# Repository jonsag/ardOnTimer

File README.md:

# ardOnTimer
An on timer with relay, mainly for use in an UV exposure box.  

Time is set with buttons and visualized on an LCD display.  

When setting new time it's saved in eeprom and reloaded at startup.  

Timer range is from 10 seconds to 9 hours, 59 minutes and 59 seconds in 10 seconds steps.  
This can be changed in configuration file.  

Parts list
==========
1 x Arduino Uno, kjell.com art#88860  
1 x LCD display 2x16 characters, kjell.com art# 90215  
1 x Relay module KY-019, kjell.com art# 87878  
1 x Buzzer, kjell.com art# 87887  
4 x Switch, kjell.com art# 36011  
1 x 10kohm potentiometer  
4 x 10kohm resistor  
1 x 220ohm resistor  
1x 100ohm resistor  

Screens
==========
The timer has three screens.  
Second row on screens shows which buttons are active.  

Standby screen
----------
Waiting for start or set.  

 * Start/Stop/Store button to start timer and enter run screen.  
 * Set button to enter set screen.  

Run screen
----------
Shows spinning bar and time left on first row, and progressbar on the second.  

 * Start/Stop/Store button to stop timer and go back to standby screen.  

Set screen
----------
Setting timer.  

* Start/Stop/Store button to store set time.  
* Set button to exit back to standby screen. If set time was not stored, previous time will be used.  
* Up or Down button to increase/decrease time. Each press adds/subtracts 10 seconds from time. Long press adds/subtracts one minute from time. Holding down button keeps stepping minutes.

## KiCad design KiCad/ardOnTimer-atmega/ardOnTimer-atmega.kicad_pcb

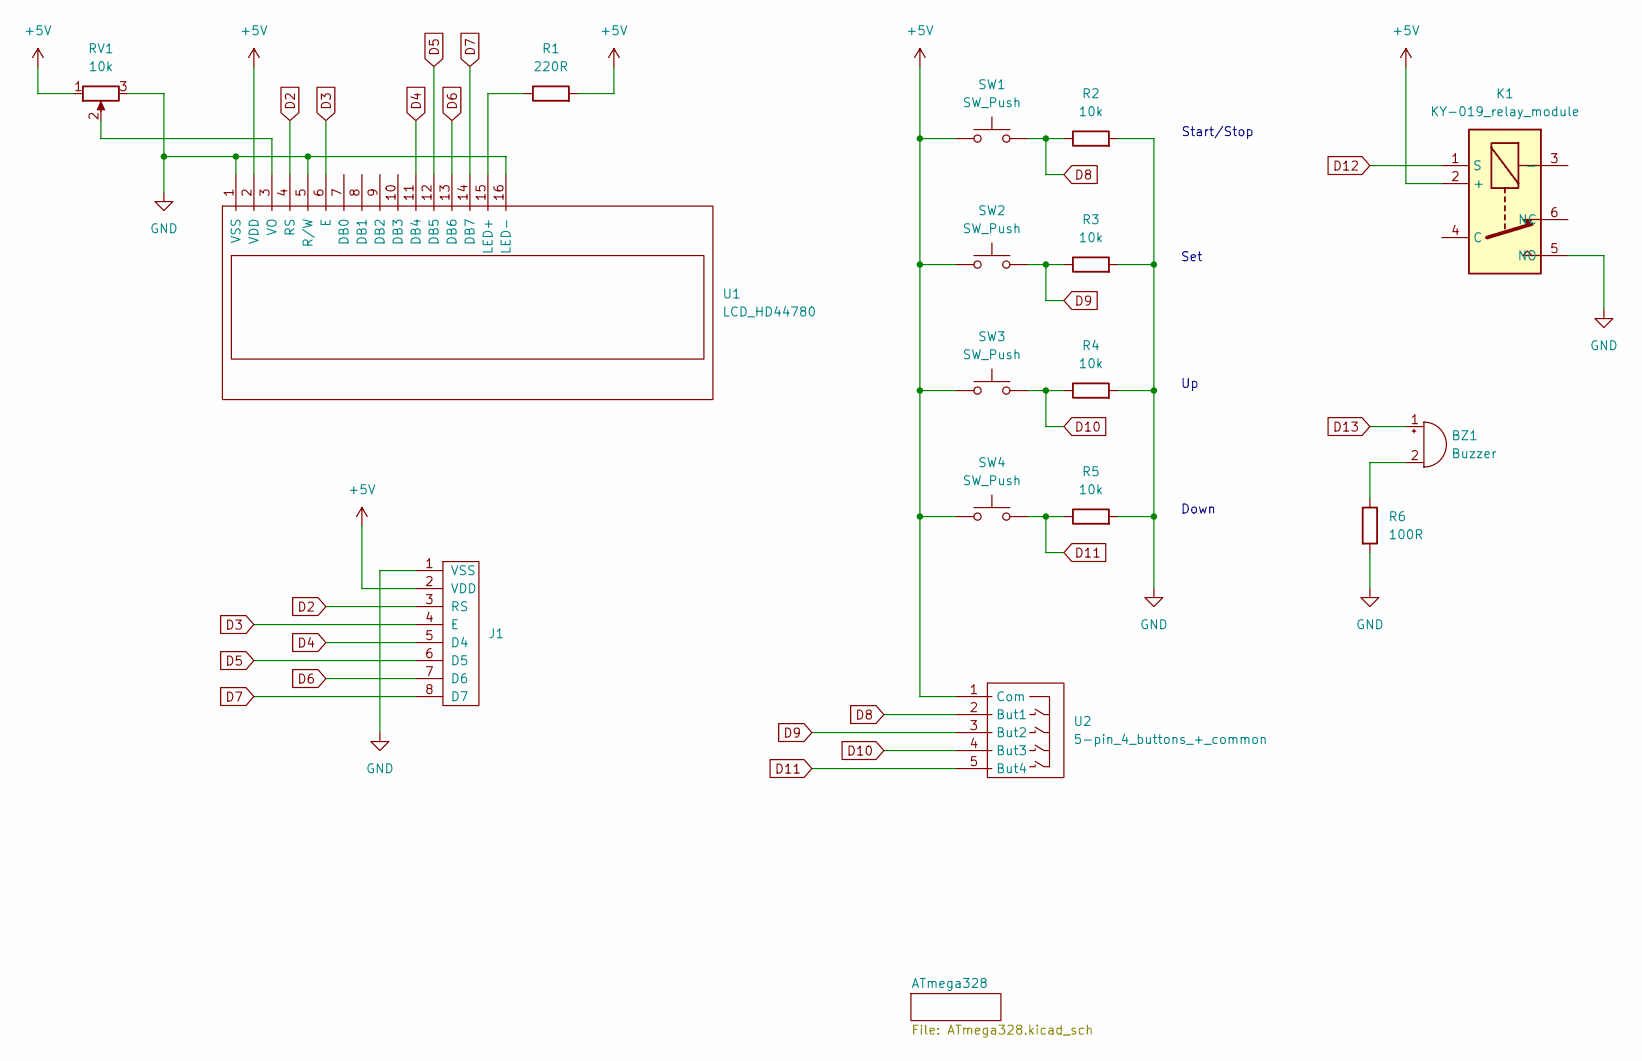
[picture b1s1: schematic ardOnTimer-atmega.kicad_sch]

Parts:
BZ1: Buzzer; Buzzer_TDK_PS1240P02BT_D12.2mm_H6.5mm_large
J1: 8-pin_header_LCD_interface; 8-pin JST LCD
K1: KY-019_relay_module; KY-019_Relay_module_w_header_large
R1: 220R; R_Axial_DIN0207_L6.3mm_D2.5mm_P10.16mm_Horizontal_larger_pa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
R2, R3, R4, R5: 10k; R_Axial_DIN0207_L6.3mm_D2.5mm_P10.16mm_Horizontal_larger_pa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
R6: 100R; R_Axial_DIN0207_L6.3mm_D2.5mm_P10.16mm_Horizontal_larger_pa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
RV1: 10k; Potentiometer_Bourns_3339P_Vertical_large
SW1, SW2, SW3, SW4: SW_Push; SW_PUSH_6mm_large
U1: LCD_HD44780; LCD_HD44780_16x2_w_headers_large
U2: 5-pin_4_buttons_+_common; 5-pin JST 4 buttons + common

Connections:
+5V: J1.2 (VDD), K1.2 (+), R1.2, RV1.1, SW1.1, SW2.1, SW3.1, SW4.1, U1.2 (VDD), U2.1 (Com); also elsewhere on the board
D2: J1.3 (RS), U1.4 (RS); also elsewhere on the board
D3: J1.4 (E), U1.6 (E); also elsewhere on the board
D4: J1.5 (D4), U1.11 (DB4); also elsewhere on the board
D5: J1.6 (D5), U1.12 (DB5); also elsewhere on the board
D6: J1.7 (D6), U1.13 (DB6); also elsewhere on the board
D7: J1.8 (D7), U1.14 (DB7); also elsewhere on the board
D8: R2.1, SW1.2, U2.2 (But1); also elsewhere on the board
D9: R3.1, SW2.2, U2.3 (But2); also elsewhere on the board
D10: R4.1, SW3.2, U2.4 (But3); also elsewhere on the board
D11: R5.1, SW4.2, U2.5 (But4); also elsewhere on the board
D12: K1.1 (S); also elsewhere on the board
D13: BZ1.1 (-); also elsewhere on the board
GND: J1.1 (VSS), K1.5 (NO), R2.2, R3.2, R4.2, R5.2, R6.2, RV1.3, U1.1 (VSS), U1.5 (R/W), U1.16 (LED-); also elsewhere on the board
unnamed: BZ1.2 (+), R6.1
unnamed: R1.1, U1.15 (LED+)
unnamed: RV1.2, U1.3 (VO)

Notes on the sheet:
Start/Stop
Down
Set

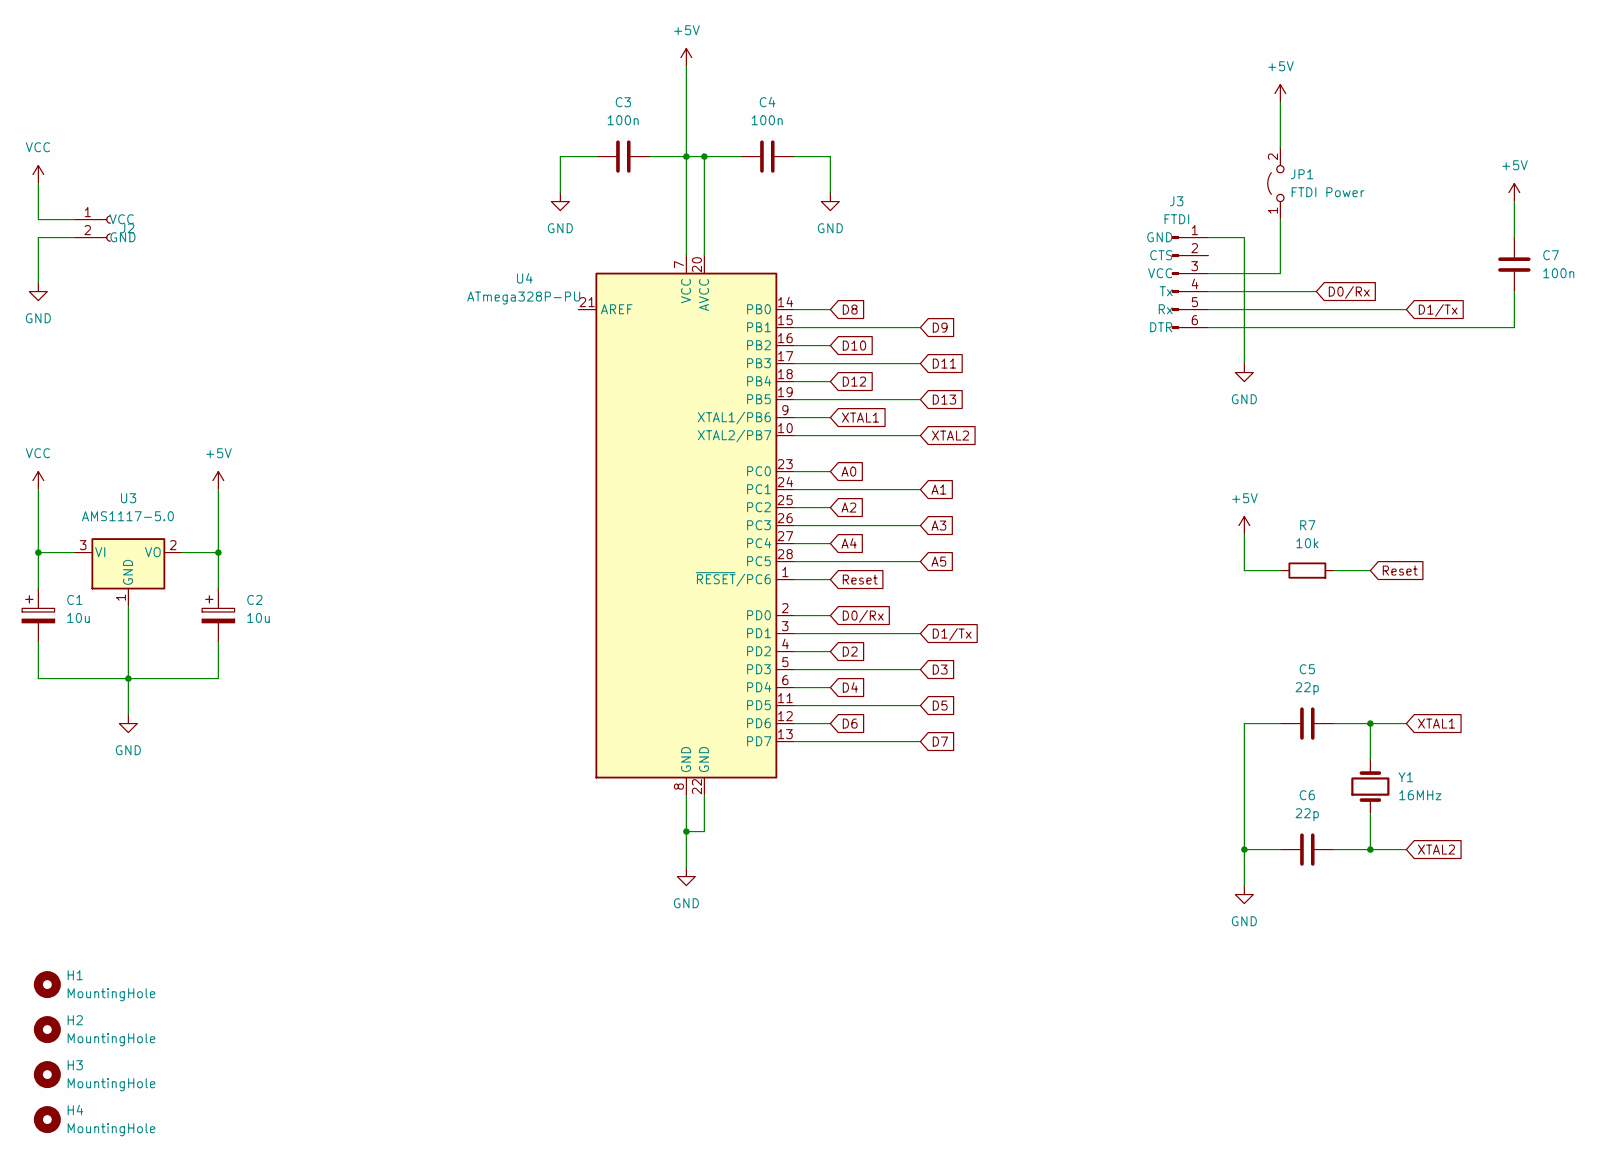
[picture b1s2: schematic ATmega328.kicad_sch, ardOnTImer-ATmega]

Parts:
C1, C2: 10u; CP_Radial_D5.0mm_P2.00mm_larger
C3, C4, C7: 100n; C_Disc_D4.3mm_W1.9mm_P5.00mm_large
C5, C6: 22p; C_Disc_D3.0mm_W1.6mm_P2.50mm_larg
H1, H2, H3, H4: MountingHole; MountingHole_3.2mm_M3
J2: Power in; BarrelJack_Horizontal
J3: FTDI; 6-pin FTDI Programmer PinSocket large
JP1: FTDI Power; Jumper_1x02_P2.54mm_large
R7: 10k; R_Axial_DIN0207_L6.3mm_D2.5mm_P10.16mm_Horizontal_larger_pa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
U3: AMS1117-5.0; SOT-223-3_TabPin2
U4: ATmega328P-PU; DIP-28_W7.62mm_LongPads w socket
Y1: 16MHz; Crystal_HC49-4H_Vertical_large

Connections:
+5V: C2.1, C3.1, C4.2, C7.2, JP1.2 (B), R7.1, U3.2 (VO), U4.7 (VCC), U4.20 (AVCC); also elsewhere on the board
A0: U4.23 (PC0)
A1: U4.24 (PC1)
A2: U4.25 (PC2)
A3: U4.26 (PC3)
A4: U4.27 (PC4)
A5: U4.28 (PC5)
D0/Rx: J3.4 (Tx), U4.2 (PD0)
D1/Tx: J3.5 (Rx), U4.3 (PD1)
D2: U4.4 (PD2); also elsewhere on the board
D3: U4.5 (PD3); also elsewhere on the board
D4: U4.6 (PD4); also elsewhere on the board
D5: U4.11 (PD5); also elsewhere on the board
D6: U4.12 (PD6); also elsewhere on the board
D7: U4.13 (PD7); also elsewhere on the board
D8: U4.14 (PB0); also elsewhere on the board
D9: U4.15 (PB1); also elsewhere on the board
D10: U4.16 (PB2); also elsewhere on the board
D11: U4.17 (PB3); also elsewhere on the board
D12: U4.18 (PB4); also elsewhere on the board
D13: U4.19 (PB5); also elsewhere on the board
GND: C1.2, C2.2, C3.2, C4.1, C5.1, C6.1, J2.2 (GND), J3.1 (GND), U3.1 (GND), U4.8 (GND), U4.22 (GND); also elsewhere on the board
unnamed: C7.1, J3.6 (DTR)
unnamed: J3.3 (VCC), JP1.1 (A)
Reset: R7.2, U4.1 (~RESET/PC6)
VCC: C1.1, J2.1 (VCC), U3.3 (VI)
XTAL1: C5.2, U4.9 (XTAL1/PB6), Y1.2
XTAL2: C6.2, U4.10 (XTAL2/PB7), Y1.1

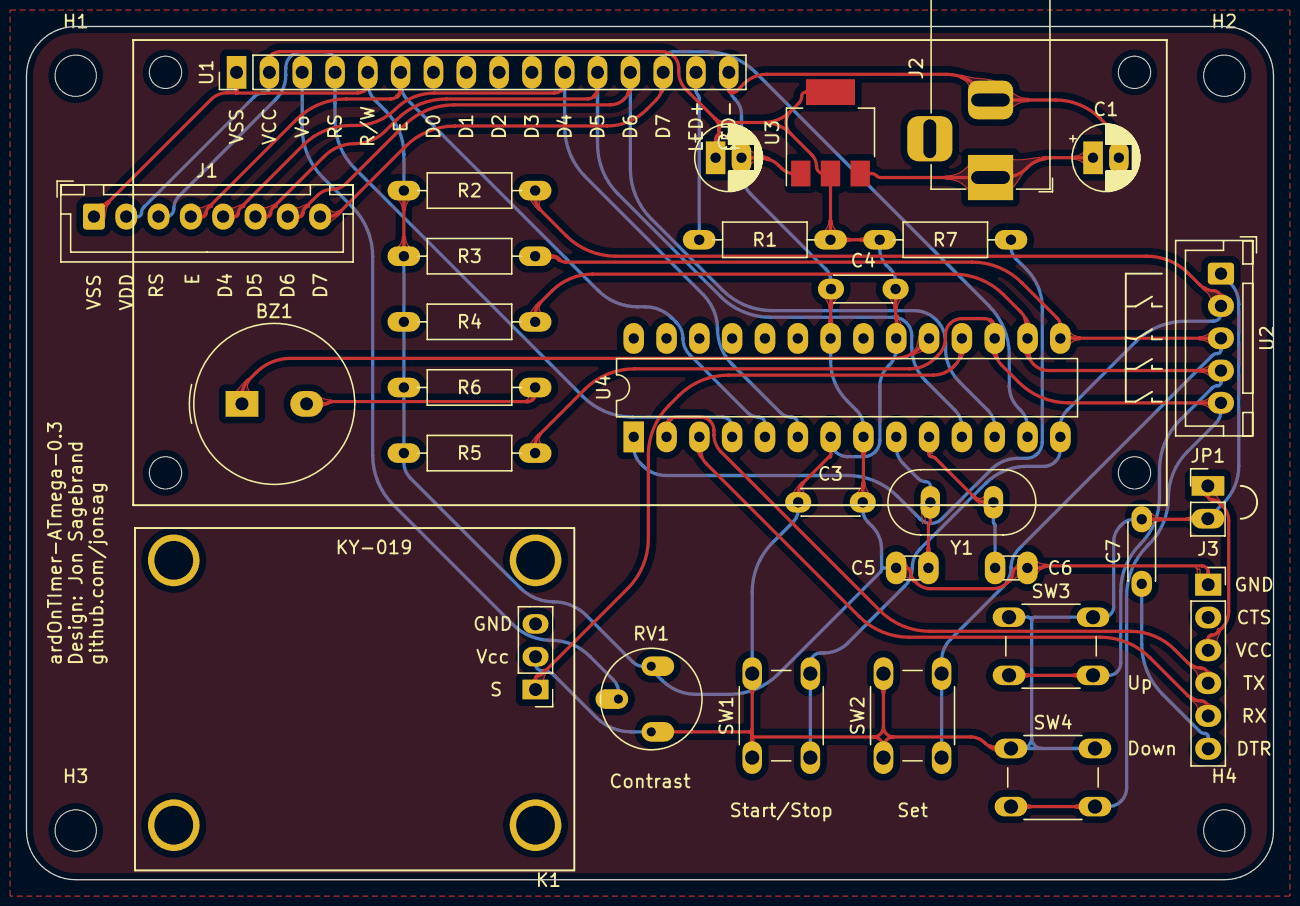
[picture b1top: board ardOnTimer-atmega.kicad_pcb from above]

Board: 2 copper layers, 96.5 x 66.0 mm, 34 parts (0 on the bottom side), 25 nets.

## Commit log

2020-01-26 added example
2020-01-26 deleted files
2020-01-26 added sketch
2020-01-26 split code
2020-01-27 sketch update
2020-01-28 mostly working sketch
2020-01-28 forgot some .h
2020-01-28 added Eagle schematics
2020-01-29 Sketch stores new value in eeprom. Enhanced lcd layout
2020-01-29 Output change. Bugs
2020-01-30 added some experimental code for increasing set speed, not implemented
2020-01-30 now speeds up when holding up/down buttons
2020-01-30 Animates run. Up, down arrows. Fast setting.
2020-01-30 Addded progress bar (not tested yet)
2020-01-30 bugs
2020-01-31 Progressbar working
2020-01-31 Deleted older project
2020-01-31 Switched DI12<->DI13
2020-01-31 deleted unnecessary files
2020-01-31 deleted unnecessary file
2020-01-31 Forgot resistor in schematics. Updated readme.
2022-08-28 kicad schematics
2022-09-09 kicad
2022-10-21 kicad v0.3
